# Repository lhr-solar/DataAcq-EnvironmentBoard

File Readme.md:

# DataAcq-EnvironmentBoard
Author: Ravi Shah  
Documentation: https://cloud.wikis.utexas.edu/wiki/spaces/LHRSOLAR/pages/205226271/Data+Acquisition+Environment+Board

The Data Acquisition Environment Board measures environmental data throughout the car, including relative humidity, airflow, and temperature. It interfaces with a Peripheral System-On-Module (SOM) to process data and transmit it via the Data Acquisition CAN bus.

## BOM
IBOM: Hardware/BOM/ibom.html (download and view in browser)  
Mouser Cart: https://www.mouser.com/ProjectManager/ProjectDetail.aspx?AccessID=8fef7b51e5

## Connectors
| # | Name | Type | Ideal Voltage | Notes |
| - | - | - | - | - |
| U4  | PSOM Connection | 53307-2471 Female |N/A | 3.65mm tall |
| J2  | CAN Output | MicroFit3.0_1x4xP3.00mm_PolarizingPeg_Vertical Female |+12V | 6.98mm tall |
| J3  | CAN Input | MicroFit3.0_1x4xP3.00mm_PolarizingPeg_Vertical Female | +12V | 6.98mm tall |
| J6  | Breakout | Nano-Fit_105310-xx10_2x05_P2.50mm_Vertical Female | +3.3V | 9.05mm tall |

## PCB

## Schematic

## Additional Notes
- I know the connectors aren't numbered right, will fix in next iteration.  
- For production use (on the car), each main environment board will interface with a breakout board containing relevant sensors to the system being monitored. Wire harnessing should minimize the distance between the main board and the breakout to prevent noise. Main boards will be connected via EnvironmentCAN to each other and to the Data Acquisition leader board.
- Not all sensors need to be present, only necessary sensors should be soldered to the board/breakout according to system needs.

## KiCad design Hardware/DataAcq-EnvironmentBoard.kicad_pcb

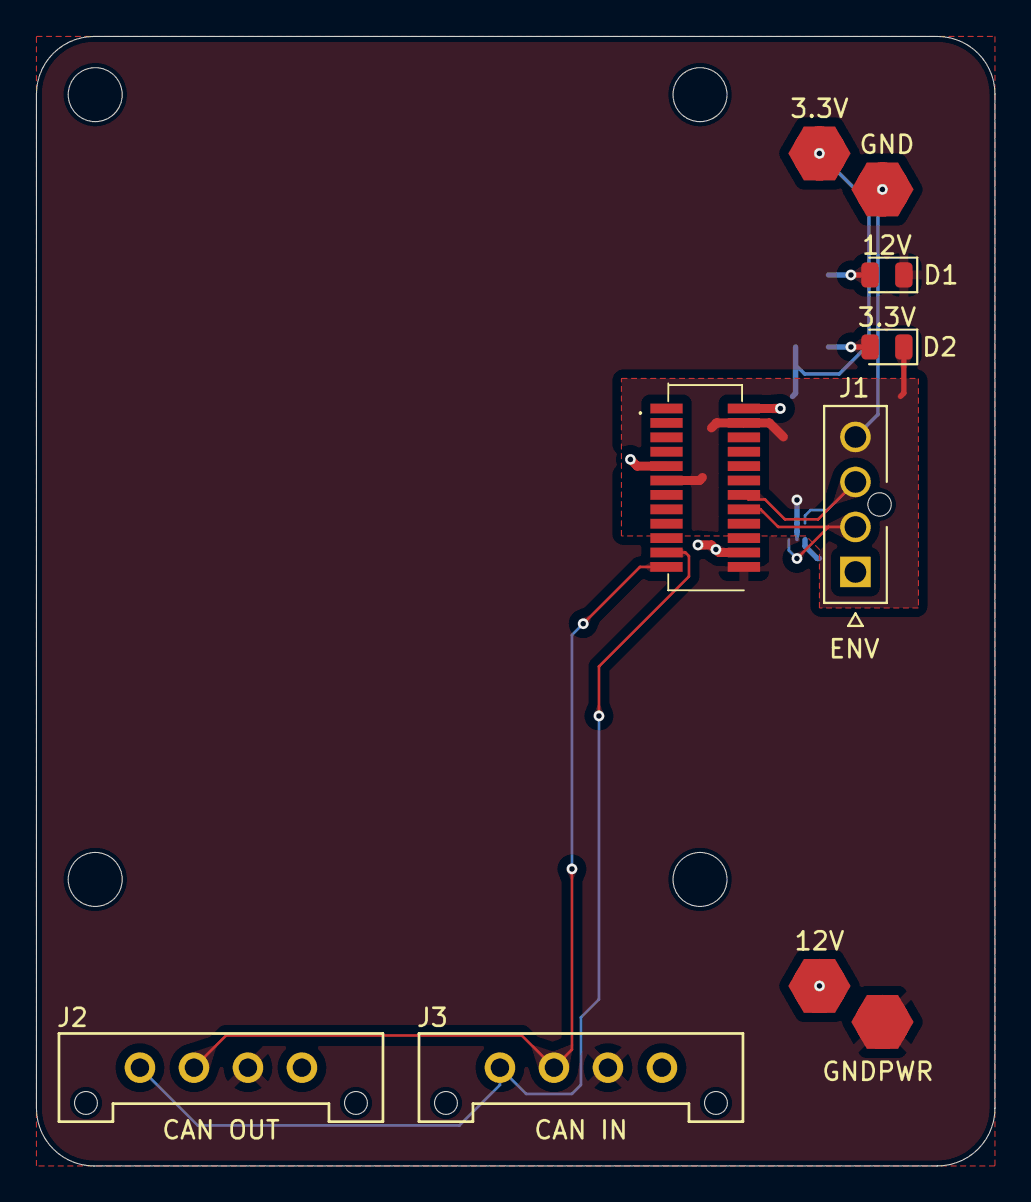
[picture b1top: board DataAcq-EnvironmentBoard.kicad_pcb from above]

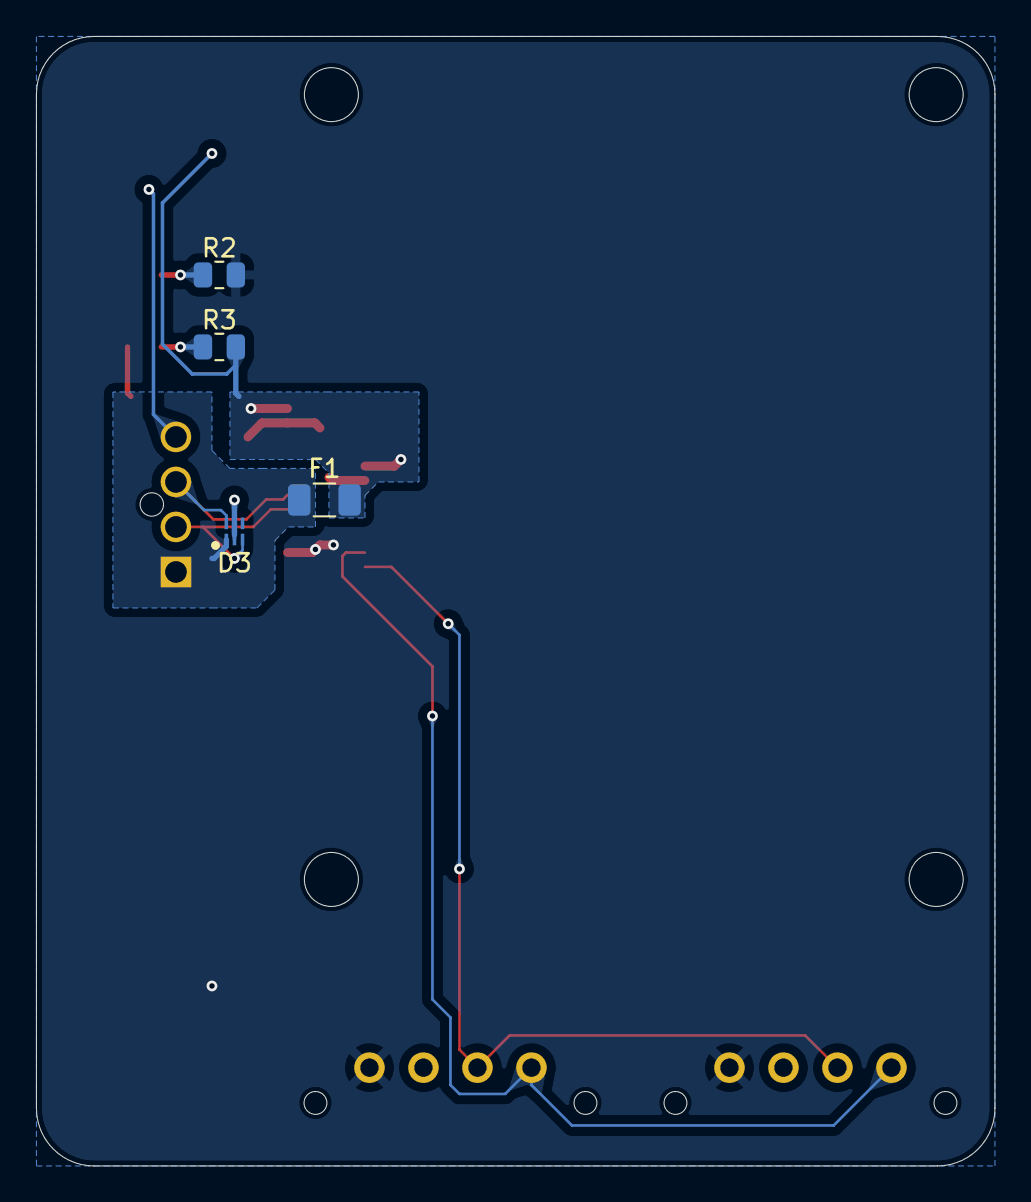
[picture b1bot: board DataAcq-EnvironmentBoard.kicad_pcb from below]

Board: 2 copper layers, 53.2 x 62.8 mm, 17 parts (4 on the bottom side), 11 nets.

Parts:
D1: 12V; LED_0805_2012Metric
D2: 3.3V; LED_0805_2012Metric
D3: PESD3V3L4BHCYL; SON45P80X130X43-6N
F1: 250mA; Fuse_1206_3216Metric
J1: ENV; MOLEX_1053091104
J2: CAN OUT; Molex_MicroFit3.0_1x4xP3.00mm_PolarizingPeg_Vertical
J3: CAN IN; Molex_MicroFit3.0_1x4xP3.00mm_PolarizingPeg_Vertical
LOGO2: Dr. Hallock; Hallock_Image_Tiny
LOGO3: UTSVT Logo; UTSVT_Logo_Symbol
LOGO4: Wolf; wolf
R2: 5.1k; R_0805_2012Metric
R3: 680; R_0805_2012Metric
TP1: 12V; TestPoint_HEX_3mmID
TP2: GNDPWR; TestPoint_HEX_3mmID
TP4: 3.3V; TestPoint_HEX_3mmID
TP5: GND; TestPoint_HEX_3mmID
U4: Daughterboard Connector; PeripheralSOM

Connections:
+3.3V: F1.1, R3.1, TP4.1, U4.2 (+3.3V), U4.9 (+3.3V)
+3.3V_OUT: D3.1 (K1), F1.2, J1.1
+12V: J2.1 (12V), J3.1 (12V), R2.1, TP1.1, U4.22 (+12V_In)
/CAN_H: J2.3 (CAN_H), J3.3 (CAN_H), U4.23 (CAN_H)
/CAN_L: J2.4 (CAN_L), J3.4 (CAN_L), U4.21 (CAN_L)
/I2C1_SCL: D3.6 (K4), J1.3, U4.14 (I2C1_SCL)
/I2C1_SDA: D3.3 (K2), J1.2, U4.16 (I2C1_SDA)
GND: D2.1 (K), D3.2 (CC_1), D3.5 (CC_2), J1.4, TP5.1, U4.4 (GND), U4.11 (GND)
GNDPWR: D1.1 (K), J2.2 (GNDPWR), J3.2 (GNDPWR), TP2.1, U4.24 (GNDPWR)
unnamed: D1.2 (A), R2.2
unnamed: D2.2 (A), R3.2

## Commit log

2024-10-05 Create LICENSE
2024-10-05 create initial KiCad project
2024-10-05 add schematic for humidity, airfow, temp sensors
2024-10-11 add connector for PSOM
2024-10-12 add CAN connector
2024-10-12 add second CAN connector and fix analog gnd
2024-10-12 thanks lakshay
2024-10-12 start laying stuff out
2024-10-12 fix labels
2024-10-12 initial layout/routing
2024-10-14 layout again
2024-10-14 add LEDs/testpoints to sch
2024-10-14 test points
2024-10-14 part numbers smh
2024-10-14 fix ground pad
2024-10-14 dumbass labels
2024-10-15 rework traces
2024-10-15 group footprints properly
2024-10-15 silkscreen/spacing
2024-10-16 third times the charm (layout)
2024-10-16 routing
2024-10-17 better CAN routing
2024-10-17 remove extraneous label
2024-10-18 change sch to match new symbols
2024-10-18 fix thermal reliefs and fills
2024-10-20 add test point and redo CAN connections
2024-10-22 add images and cleanup
2024-10-22 start adding dimensions (not final)
2024-10-22 bommmm
2024-10-22 dimensisosns
2024-10-23 add 3d model
2024-10-25 add i2c testpoints to sch
2024-10-26 move passives to sensor side, reroute temp sensor
2024-10-26 add breakout board connectors to sch
2024-10-26 add TVS diodes and fuses for breakout
2024-10-26 assign footprints and PN
2024-10-27 pls be the last time i have to layout this
2024-10-27 update BOM
2024-10-27 led/model
2024-10-29 rm useless stuff
2024-10-29 start sch/layout modifications
2024-10-30 update BOM and model
2024-10-30 fix trace routing
2024-10-30 silkscreen info
2024-10-31 change sch for one connector design
2024-11-01 modify layout for new connector
2024-11-02 sch: add sensors back for testing
2024-11-02 rearrange connector to match breakout
2024-11-02 traces for connector change
2024-11-02 fix silkscreen
2024-11-03 fix pours
2024-11-03 finalize layout
2024-11-03 update 3d model
2024-11-03 gerbs
2024-11-03 correct mounting hole dimensions
2024-11-07 wtf git
2024-11-07 pls work
2024-11-07 update mouser cart link
2024-11-09 separate hardware and software
2024-11-09 fix modules
2024-11-09 touch
2024-11-09 LED test
2024-11-11 add embedded sharepoint module
2024-11-11 add initial src, inc, makefile
2024-11-14 add test i2c transmit
2024-11-14 HOLYSHITITWORKS
2024-11-15 should still work
2024-11-15 add proper delays for consistent reads
2024-11-18 move working i2c code to test folder
2024-11-21 CAN sends humidity/temp data (kinda)
2024-11-23 specify format for CAN frames and pad with zeros upon error
2024-11-30 finally figured out crc algo
2024-11-30 enum for crc validation
2024-12-02 comments :(
2024-12-02 move SHT45 polling and CAN payload into separate functions
2024-12-02 add i2c2 init (for airflow)
2024-12-03 move SHT45 driver to separate file
2024-12-03 move CAN package/send to separate file
2024-12-04 add debug folder
2024-12-07 update readme with connectors/bom
2024-12-07 update readme with sch/pcb/notes
2024-12-11 start adding FS3000 driver, not verified yet
2025-02-24 remove sensors from this board
2025-02-24 rework sch for new breakout design
2025-02-24 new ptc & footprints
2025-02-24 dumb and dumber
2025-02-24 not layout
2025-02-24 layout finished
2025-04-14 bump sharepoint + makefile changes
2025-04-14 rm uneeded stuff
2025-04-16 fix headers
2025-04-16 moved drivers to drivers
